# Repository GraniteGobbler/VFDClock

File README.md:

# VFDClock
A table clock with 7-segment VFD tubes running on an ESP32-S3 MCU.

## Showcase

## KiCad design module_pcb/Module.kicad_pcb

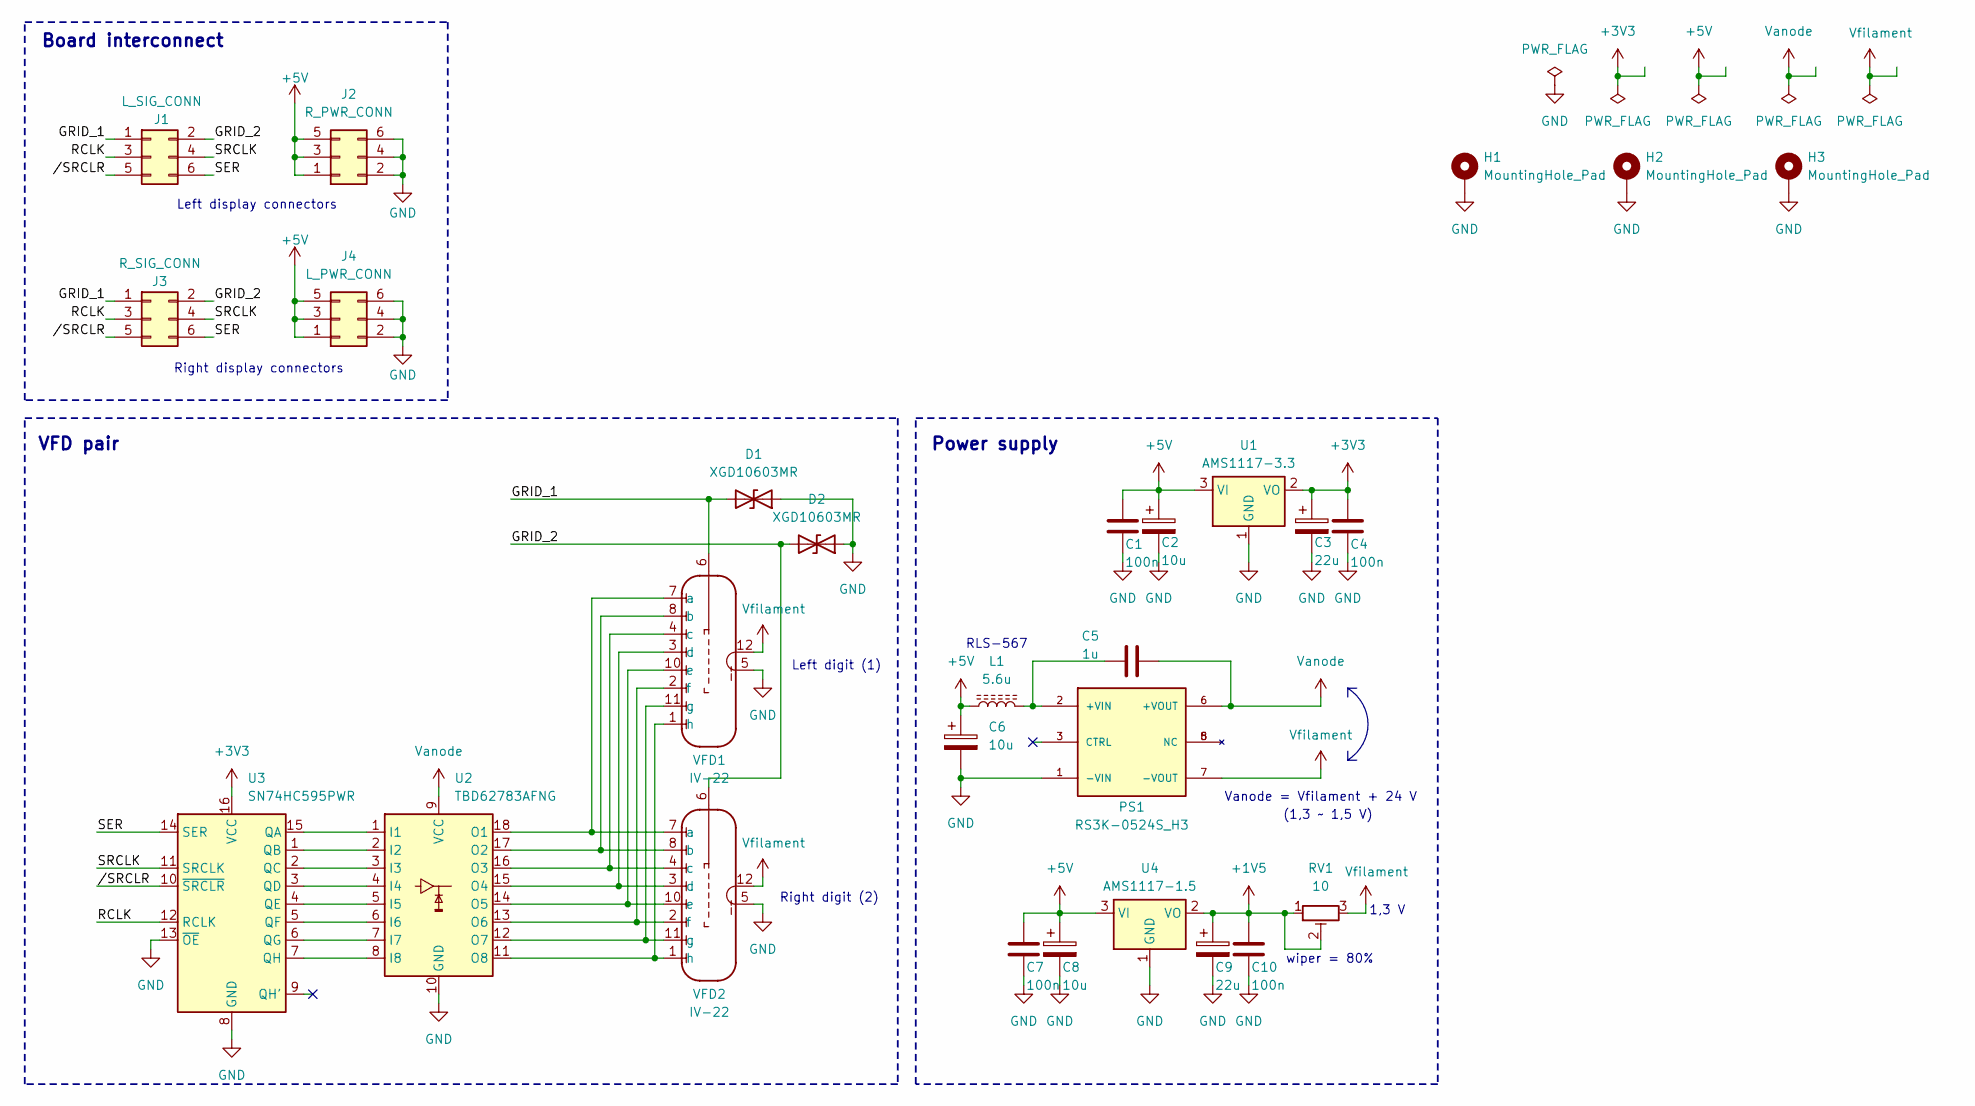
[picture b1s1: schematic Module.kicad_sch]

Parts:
C1, C4, C7, C10: 100n; C_0805_2012Metric
C2, C6, C8: 10u; CP_EIA-3216-18_Kemet-A
C3, C9: 22u; CP_EIA-3216-18_Kemet-A
C5: 1u; C_0805_2012Metric
D1, D2: XGD10603MR; D_0603_1608Metric
H1, H2, H3: MountingHole_Pad; MountingHole_3.2mm_M3_ISO14580_Pad_TopBottom
J1: L_SIG_CONN; PinSocket_2x03_P2.54mm_Horizontal
J2: R_PWR_CONN; PinSocket_2x03_P2.54mm_Horizontal
J3: R_SIG_CONN; PinSocket_2x03_P2.54mm_Horizontal
J4: L_PWR_CONN; PinSocket_2x03_P2.54mm_Horizontal
L1: 5.6u; L_1812_4532Metric
PS1: RS3K-0524S_H3; CONV_RS3K-0524S_H3; PARTREV 2-2024
RV1: 10; Potentiometer_Bourns_3339P_Vertical
U1: AMS1117-3.3; SOT-223-3_TabPin2
U2: TBD62783AFNG; SSOP-18_4.4x6.5mm_P0.65mm
U3: SN74HC595PWR; TSSOP-16_4.4x5mm_P0.65mm
U4: AMS1117-1.5; SOT-223-3_TabPin2
VFD1, VFD2: IV-22; PinSocket_1x12_P2.54mm_Vertical

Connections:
+1V5: C9.1, C10.1, RV1.1, RV1.2, U4.2 (VO)
+3V3: C3.1, C4.1, U1.2 (VO), U3.16 (VCC)
+5V: C1.1, C2.1, C6.1, C7.1, C8.1, J2.1, J2.3, J2.5, J4.1, J4.3, J4.5, L1.1, U1.3 (VI), U4.3 (VI)
/GRID_1: D1.2 (A2), J1.1, J3.1, VFD1.6
/GRID_2: D2.2 (A2), J1.2, J3.2, VFD2.6
/RCLK: J1.3, J3.3, U3.12 (RCLK)
/SER: J1.6, J3.6, U3.14 (SER)
/SRCLK: J1.4, J3.4, U3.11 (SRCLK)
//SRCLR: J1.5, J3.5, U3.10 (~SRCLR)
GND: C1.2, C2.2, C3.2, C4.2, C6.2, C7.2, C8.2, C9.2, C10.2, D1.1 (A1), D2.1 (A1), H1.1, H2.1, H3.1, J2.2, J2.4, J2.6, J4.2, J4.4, J4.6, PS1.1 (-VIN), U1.1 (GND), U2.10 (GND), U3.8 (GND), U3.13 (~OE), U4.1 (GND), VFD1.5, VFD2.5
unnamed: C5.1, L1.2, PS1.2 (+VIN)
unnamed: U2.1 (I1), U3.15 (QA)
unnamed: U2.2 (I2), U3.1 (QB)
unnamed: U2.3 (I3), U3.2 (QC)
unnamed: U2.4 (I4), U3.3 (QD)
unnamed: U2.5 (I5), U3.4 (QE)
unnamed: U2.6 (I6), U3.5 (QF)
unnamed: U2.7 (I7), U3.6 (QG)
unnamed: U2.8 (I8), U3.7 (QH)
unnamed: U2.18 (O1), VFD1.7 (a), VFD2.7 (a)
unnamed: U2.17 (O2), VFD1.8 (b), VFD2.8 (b)
unnamed: U2.16 (O3), VFD1.4 (c), VFD2.4 (c)
unnamed: U2.15 (O4), VFD1.3 (d), VFD2.3 (d)
unnamed: U2.14 (O5), VFD1.10 (e), VFD2.10 (e)
unnamed: U2.13 (O6), VFD1.2 (f), VFD2.2 (f)
unnamed: U2.12 (O7), VFD1.11 (g), VFD2.11 (g)
unnamed: U2.11 (O8), VFD1.1 (h), VFD2.1 (h)
Vanode: C5.2, PS1.6 (+VOUT), U2.9 (VCC)
Vfilament: PS1.7 (-VOUT), RV1.3, VFD1.12, VFD2.12

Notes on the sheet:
Right digit (2)
Left digit (1)
RLS-567
Power supply
Vanode = Vfilament + 24 V
1,3 V
VFD pair
Board interconnect
wiper = 80%
(1,3 ~ 1,5 V)
Left display connectors
Right display connectors

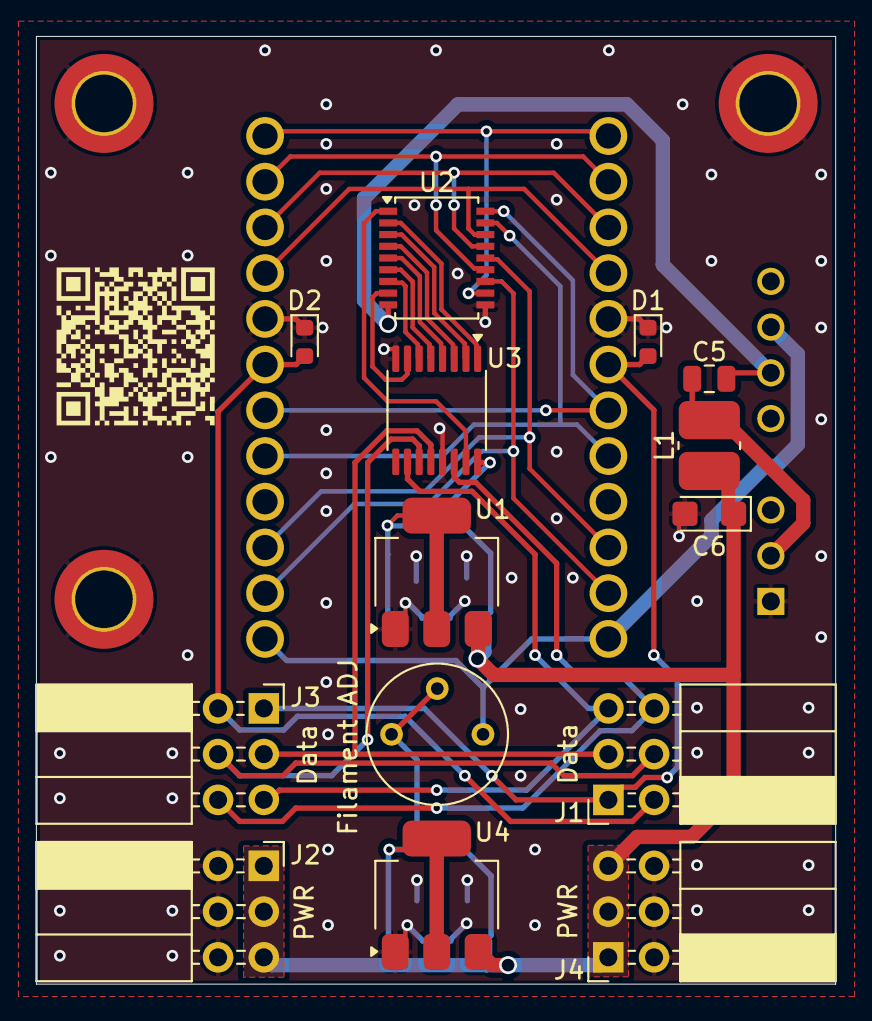
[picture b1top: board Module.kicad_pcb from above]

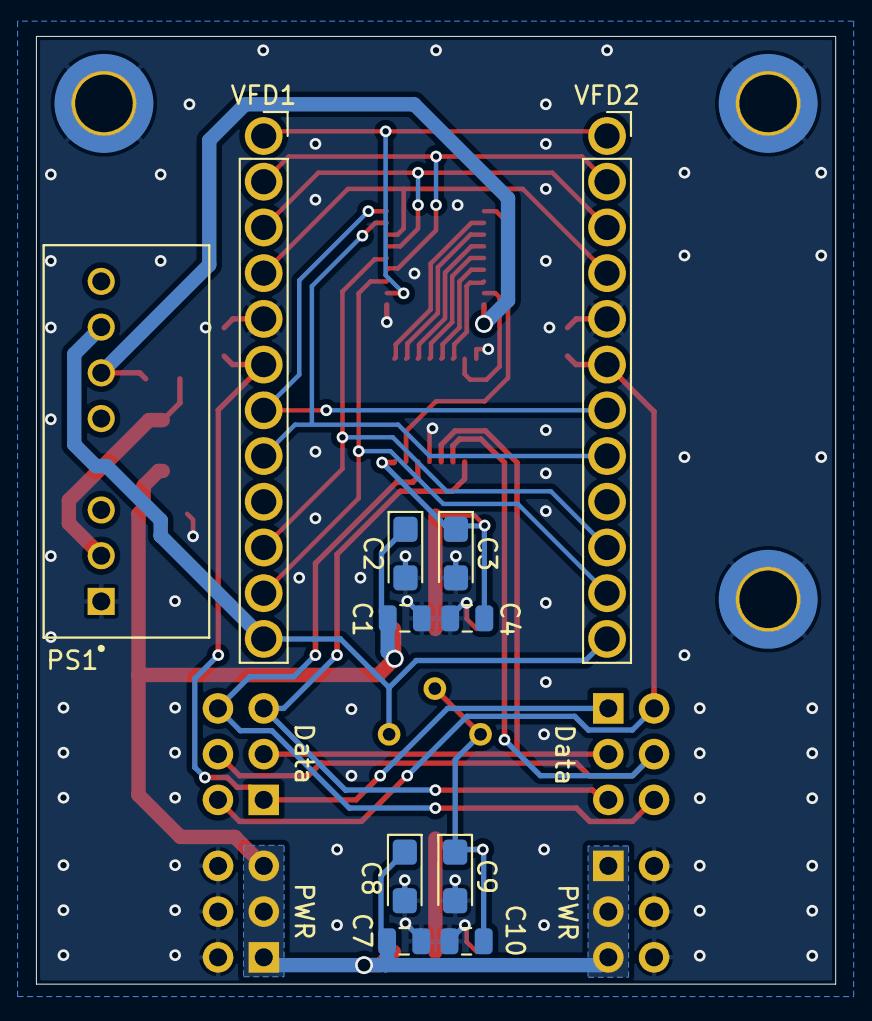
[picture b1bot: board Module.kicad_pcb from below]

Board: 2 copper layers, 44.4 x 52.7 mm, 28 parts (11 on the bottom side), 29 nets.

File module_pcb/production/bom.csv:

Designator,Footprint,Quantity,Value,LCSC Part #
"C1, C10, C4, C7",0805,4,100n,
"C2, C6, C8",CP_EIA-3216-18_Kemet-A,3,10u,
"C3, C9",CP_EIA-3216-18_Kemet-A,2,22u,
C5,0805,1,1u,
"D1, D2",0603,2,XGD10603MR,
J1,PinSocket_2x03_P2.54mm_Horizontal,1,L_SIG_CONN,
J2,PinSocket_2x03_P2.54mm_Horizontal,1,R_PWR_CONN,
J3,PinSocket_2x03_P2.54mm_Horizontal,1,R_SIG_CONN,
J4,PinSocket_2x03_P2.54mm_Horizontal,1,L_PWR_CONN,
L1,1812,1,5.6u,
PS1,CONV_RS3K-0524S_H3,1,RS3K-0524S_H3,
RV1,Potentiometer_Bourns_3339P_Vertical,1,10,
U1,SOT-223-3_TabPin2,1,AMS1117-3.3,
U2,SSOP-18_4.4x6.5mm_P0.65mm,1,TBD62783AFNG,
U3,TSSOP-16_4.4x5mm_P0.65mm,1,SN74HC595PWR,
U4,SOT-223-3_TabPin2,1,AMS1117-1.5,
"VFD1, VFD2",PinSocket_1x12_P2.54mm_Vertical,2,IV-22,

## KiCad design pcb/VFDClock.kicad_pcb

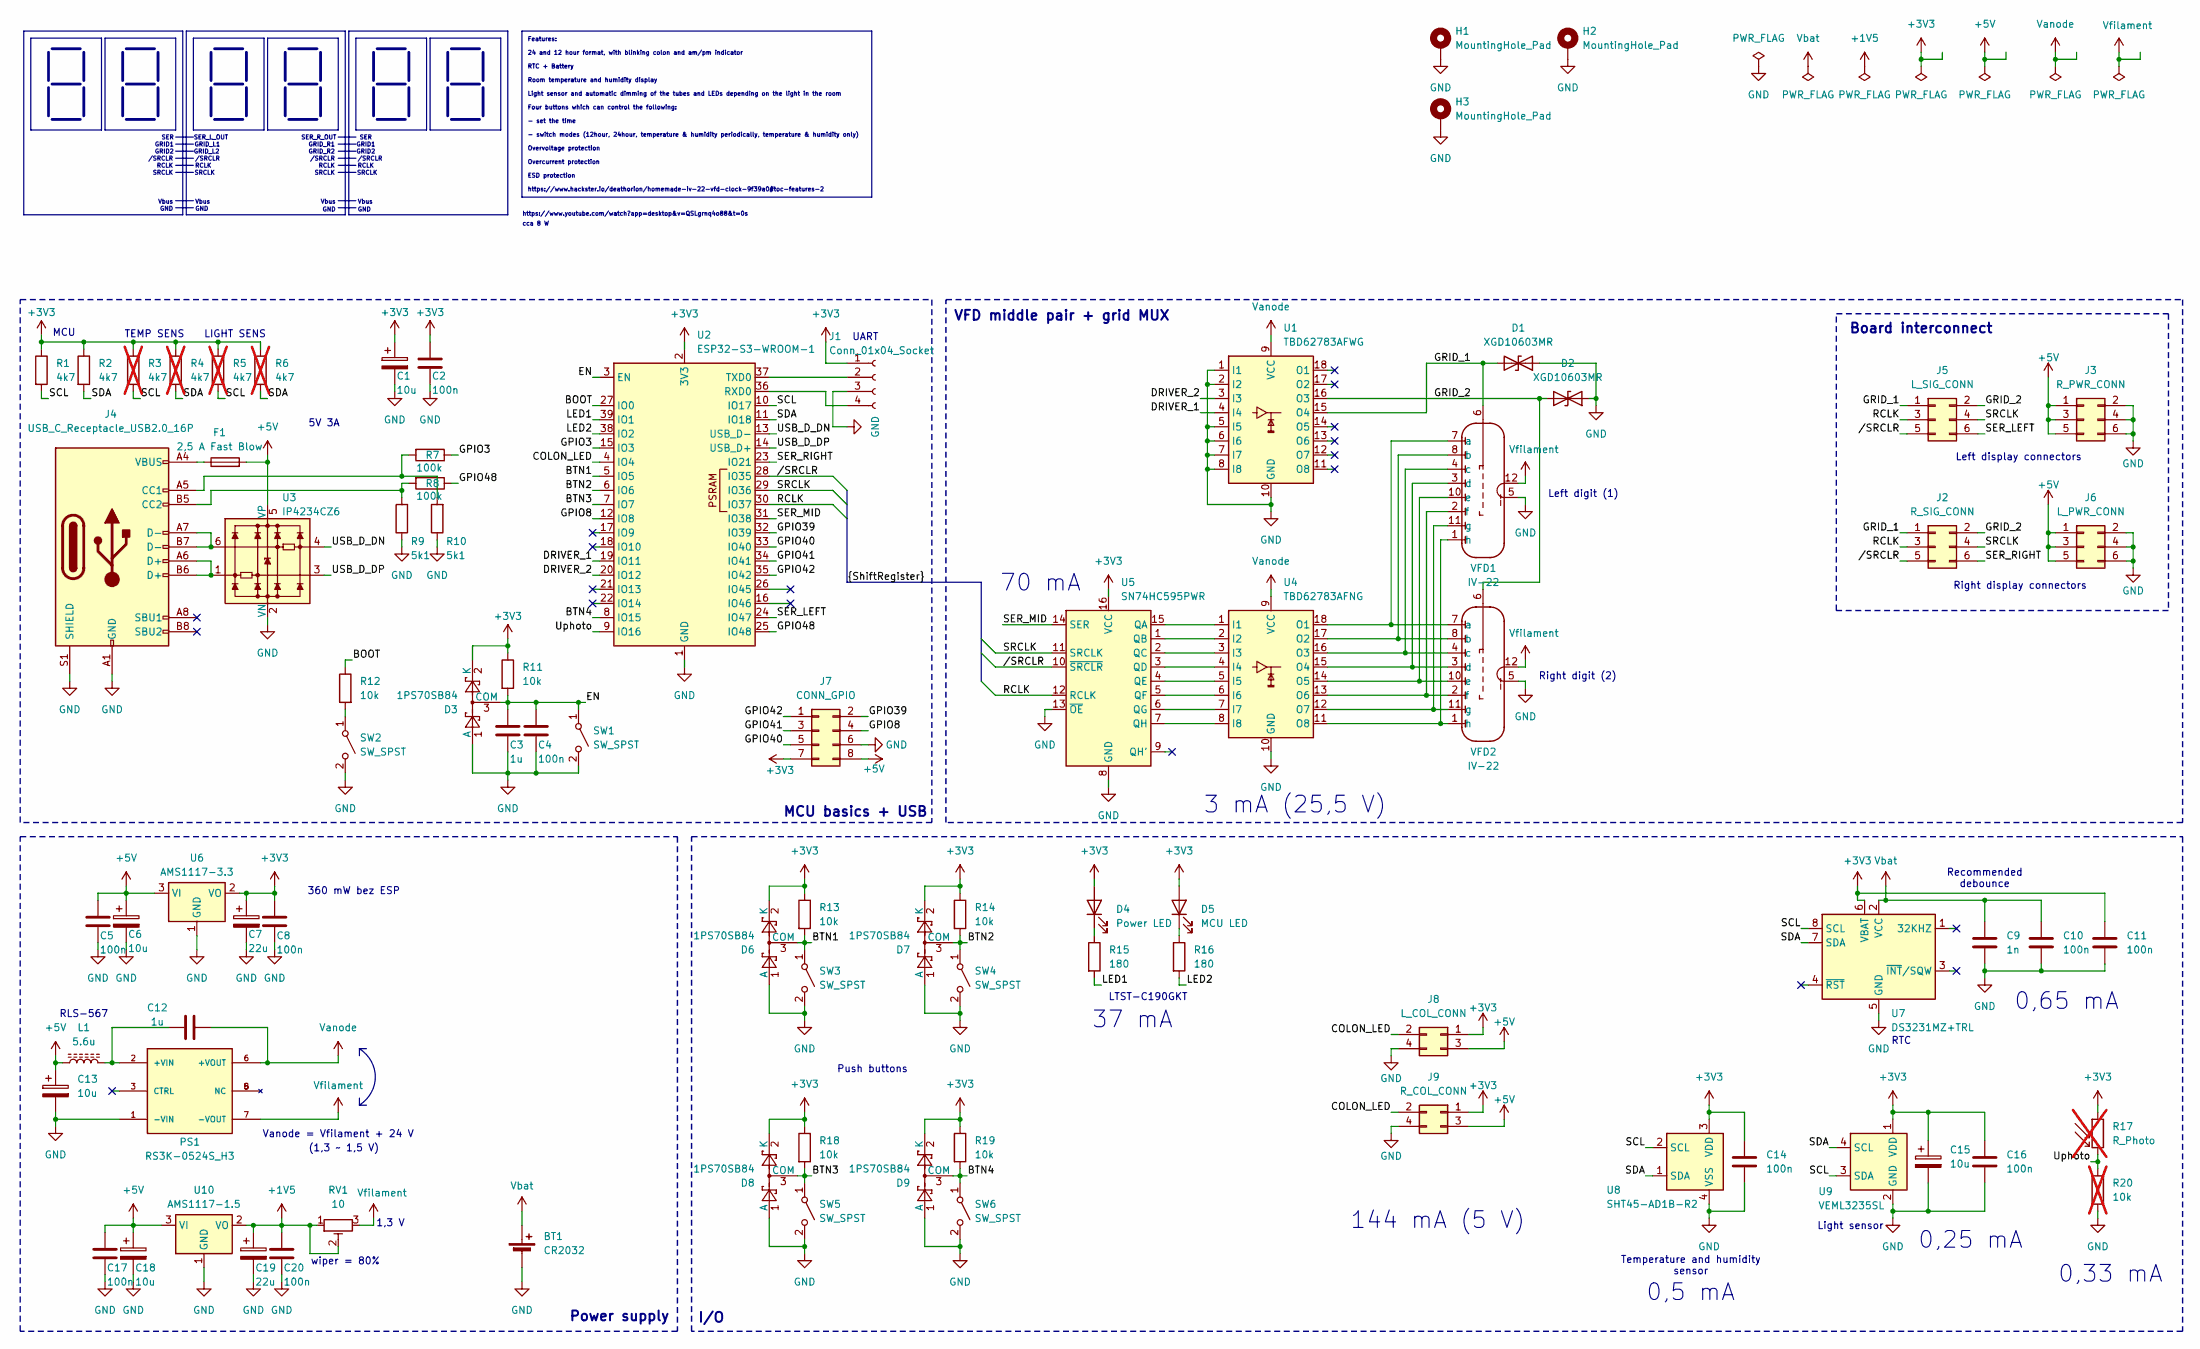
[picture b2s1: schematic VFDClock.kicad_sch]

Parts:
BT1: CR2032; BatteryHolder_Keystone_3034_1x20mm
C1, C6, C13, C15, C18: 10u; CP_EIA-3216-18_Kemet-A
C2, C4, C5, C8, C10, C11, C14, C16, C17, C20: 100n; C_0805_2012Metric
C3, C12: 1u; C_0805_2012Metric
C7, C19: 22u; CP_EIA-3216-18_Kemet-A
C9: 1n; C_0805_2012Metric
D1, D2: XGD10603MR; D_0603_1608Metric
D3, D6, D7, D8, D9: 1PS70SB84; SOT-323_SC-70
D4: Power LED; LED_0603_1608Metric
D5: MCU LED; LED_0603_1608Metric
F1: 2,5 A Fast Blow; Fuse_0603_1608Metric
H1, H2, H3: MountingHole_Pad; MountingHole_3.2mm_M3_ISO14580_Pad_TopBottom
J1: Conn_01x04_Socket; PinSocket_2x02_P2.54mm_Vertical_SMD
J2: R_SIG_CONN; PinHeader_2x03_P2.54mm_Horizontal
J3: R_PWR_CONN; PinHeader_2x03_P2.54mm_Horizontal
J4: USB_C_Receptacle_USB2.0_16P; CUI_UJ20-C-V-C-2-SMT-TR
J5: L_SIG_CONN; PinHeader_2x03_P2.54mm_Horizontal
J6: L_PWR_CONN; PinHeader_2x03_P2.54mm_Horizontal
J7: CONN_GPIO; PinSocket_2x04_P2.54mm_Vertical_SMD
J8: L_COL_CONN; JST_XH_B4B-XH-A_1x04_P2.50mm_Vertical
J9: R_COL_CONN; JST_XH_B4B-XH-A_1x04_P2.50mm_Vertical
L1: 5.6u; L_1812_4532Metric
PS1: RS3K-0524S_H3; CONV_RS3K-0524S_H3; PARTREV 2-2024
R1, R2: 4k7; R_0805_2012Metric
R3, R4, R5, R6: 4k7; R_0805_2012Metric; not fitted
R7, R8: 100k; R_0805_2012Metric
R9, R10: 5k1; R_0805_2012Metric
R11, R12, R13, R14, R18, R19: 10k; R_0805_2012Metric
R15, R16: 180; R_0805_2012Metric
R17: R_Photo; R_LDR_5.1x4.3mm_P3.4mm_Vertical; not fitted
R20: 10k; R_0805_2012Metric; not fitted
RV1: 10; Potentiometer_Bourns_3339P_Vertical
SW1, SW2: SW_SPST; SW_SPST_PTS810
SW3, SW4, SW5, SW6: SW_SPST; SW_Tactile_SPST_Angled_PTS645Vx83-2LFS
U1: TBD62783AFWG; SSOP-18_4.4x6.5mm_P0.65mm
U2: ESP32-S3-WROOM-1
U3: IP4234CZ6; SC-74-6_1.55x2.9mm_P0.95mm
U4: TBD62783AFNG; SSOP-18_4.4x6.5mm_P0.65mm
U5: SN74HC595PWR; TSSOP-16_4.4x5mm_P0.65mm
U6: AMS1117-3.3; SOT-223-3_TabPin2
U7: DS3231MZ+TRL; SOIC-8_3.9x4.9mm_P1.27mm
U8: SHT45-AD1B-R2; Sensirion_DFN-4_1.5x1.5mm_P0.8mm_SHT4x_NoCentralPad
U9: VEML3235SL; VEML3235SL_Horizontal
U10: AMS1117-1.5; SOT-223-3_TabPin2
VFD1, VFD2: IV-22; PinSocket_1x12_P2.54mm_Vertical

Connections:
+1V5: C19.1, C20.1, RV1.1, RV1.2, U10.2 (VO)
+3V3: C1.1, C2.1, C7.1, C8.1, C11.1, C14.1, C15.1, C16.1, D3.2 (K), D4.2 (A), D5.2 (A), D6.2 (K), D7.2 (K), D8.2 (K), D9.2 (K), J1.1, J7.7, J8.1, J9.1, R1.1, R2.1, R3.1, R4.1, R5.1, R6.1, R11.1, R13.1, R14.1, R17.1, R18.1, R19.1, U2.2 (3V3), U5.16 (VCC), U6.2 (VO), U7.6 (VBAT), U8.3 (VDD), U9.1 (VDD)
+5V: C5.1, C6.1, C13.1, C17.1, C18.1, F1.2, J3.1, J3.3, J3.5, J6.1, J6.3, J6.5, J7.8, J8.3, J9.3, L1.1, U3.5 (VP), U6.3 (VI), U10.3 (VI)
/BOOT: R12.1, U2.27 (IO0)
/BTN1: D6.3 (COM), R13.2, SW3.1 (A), U2.5 (IO5)
/BTN2: D7.3 (COM), R14.2, SW4.1 (A), U2.6 (IO6)
/BTN3: D8.3 (COM), R18.2, SW5.1 (A), U2.7 (IO7)
/BTN4: D9.3 (COM), R19.2, SW6.1 (A), U2.8 (IO15)
/COLON_LED: J8.2, J9.2, U2.4 (IO4)
/DRIVER_1: U1.4 (I4), U2.19 (IO11)
/DRIVER_2: U1.3 (I3), U2.20 (IO12)
/EN: C3.1, C4.1, D3.3 (COM), R11.2, SW1.1 (A), U2.3 (EN)
/GPIO3: R7.1, U2.15 (IO3)
/GPIO8: J7.4, U2.12 (IO8)
/GPIO39: J7.2, U2.32 (IO39)
/GPIO40: J7.5, U2.33 (IO40)
/GPIO41: J7.3, U2.34 (IO41)
/GPIO42: J7.1, U2.35 (IO42)
/GPIO48: R8.1, U2.25 (IO48)
/GRID_1: D1.2 (A2), J2.1, J5.1, U1.15 (O4), VFD1.6
/GRID_2: D2.2 (A2), J2.2, J5.2, U1.16 (O3), VFD2.6
/LED1: R15.2, U2.39 (IO1)
/LED2: R16.2, U2.38 (IO2)
/RCLK: J2.3, J5.3, U2.30 (IO37), U5.12 (RCLK)
/SCL: R1.2, R3.2, R5.2, U2.10 (IO17), U7.8 (SCL), U8.2 (SCL), U9.3 (SDA)
/SDA: R2.2, R4.2, R6.2, U2.11 (IO18), U7.7 (SDA), U8.1 (SDA), U9.4 (SCL)
/SER_LEFT: J5.6, U2.24 (IO47)
/SER_MID: U2.31 (IO38), U5.14 (SER)
/SER_RIGHT: J2.6, U2.23 (IO21)
/SRCLK: J2.4, J5.4, U2.29 (IO36), U5.11 (SRCLK)
/USB_D_DN: U2.13 (USB_D-), U3.4
/USB_D_DP: U2.14 (USB_D+), U3.3
/Uphoto: R17.2, R20.1, U2.9 (IO16)
//SRCLR: J2.5, J5.5, U2.28 (IO35), U5.10 (~SRCLR)
GND: BT1.2 (-), C1.2, C2.2, C3.2, C4.2, C5.2, C6.2, C7.2, C8.2, C9.2, C10.2, C11.2, C13.2, C14.2, C15.2, C16.2, C17.2, C18.2, C19.2, C20.2, D1.1 (A1), D2.1 (A1), D3.1 (A), D6.1 (A), D7.1 (A), D8.1 (A), D9.1 (A), H1.1, H2.1, H3.1, J1.3, J3.2, J3.4, J3.6, J4.A1 (GND), J4.A12 (GND), J4.B1 (GND), J4.B12 (GND), J4.S1 (SHIELD), J6.2, J6.4, J6.6, J7.6, J8.4, J9.4, PS1.1 (-VIN), R9.1, R10.1, R20.2, SW1.2 (B), SW2.2 (B), SW3.2 (B), SW4.2 (B), SW5.2 (B), SW6.2 (B), U1.1 (I1), U1.2 (I2), U1.5 (I5), U1.6 (I6), U1.7 (I7), U1.8 (I8), U1.10 (GND), U2.1 (GND), U2.40 (GND), U2.41 (GND), U3.2 (VN), U4.10 (GND), U5.8 (GND), U5.13 (~OE), U6.1 (GND), U7.5 (GND), U8.4 (VSS), U9.2 (GND), U10.1 (GND), VFD1.5, VFD2.5
unnamed: D4.1 (K), R15.1
unnamed: D5.1 (K), R16.1
unnamed: F1.1, J4.A4 (VBUS), J4.A9 (VBUS), J4.B4 (VBUS), J4.B9 (VBUS)
unnamed: J1.2, U2.37 (TXD0)
unnamed: J1.4, U2.36 (RXD0)
unnamed: J4.A5 (CC1), R7.2, R10.2
unnamed: J4.B5 (CC2), R8.2, R9.2
unnamed: J4.A6 (D+), J4.B6 (D+), U3.1
unnamed: J4.A7 (D-), J4.B7 (D-), U3.6
unnamed: C12.1, L1.2, PS1.2 (+VIN)
unnamed: R12.2, SW2.1 (A)
unnamed: U4.1 (I1), U5.15 (QA)
unnamed: U4.2 (I2), U5.1 (QB)
unnamed: U4.3 (I3), U5.2 (QC)
unnamed: U4.4 (I4), U5.3 (QD)
unnamed: U4.5 (I5), U5.4 (QE)
unnamed: U4.6 (I6), U5.5 (QF)
unnamed: U4.7 (I7), U5.6 (QG)
unnamed: U4.8 (I8), U5.7 (QH)
unnamed: U4.18 (O1), VFD1.7 (a), VFD2.7 (a)
unnamed: U4.17 (O2), VFD1.8 (b), VFD2.8 (b)
unnamed: U4.16 (O3), VFD1.4 (c), VFD2.4 (c)
unnamed: U4.15 (O4), VFD1.3 (d), VFD2.3 (d)
unnamed: U4.14 (O5), VFD1.10 (e), VFD2.10 (e)
unnamed: U4.13 (O6), VFD1.2 (f), VFD2.2 (f)
unnamed: U4.12 (O7), VFD1.11 (g), VFD2.11 (g)
unnamed: U4.11 (O8), VFD1.1 (h), VFD2.1 (h)
Vanode: C12.2, PS1.6 (+VOUT), U1.9 (VCC), U4.9 (VCC)
Vbat: BT1.1 (+), C9.1, C10.1, U7.2 (VCC)
Vfilament: PS1.7 (-VOUT), RV1.3, VFD1.12, VFD2.12

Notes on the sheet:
TEMP SENS
0,5 mA
Right digit (2)
GRID_R2
3 mA (25,5 V)
0,65 mA
Left digit (1)
Vbus
Push buttons
SRCLK
RTC
Temperature and humidity sensor
RLS-567
MCU
Power supply
UART
GND
0,25 mA
37 mA
GRID2
Vanode = Vfilament + 24 V
RCLK
1,3 V
VFD middle pair + grid MUX
MCU basics + USB
SER_R_OUT
Board interconnect
GRID_R1
SER_L_OUT
wiper = 80%
(1,3 ~ 1,5 V)
144 mA (5 V)
/SRCLR
GRID1
https://www.youtube.com/watch?app=desktop&v=QSLgrnq4o88&t=0s
I/O
LIGHT SENS
GRID_L1
SER
GRID_L2

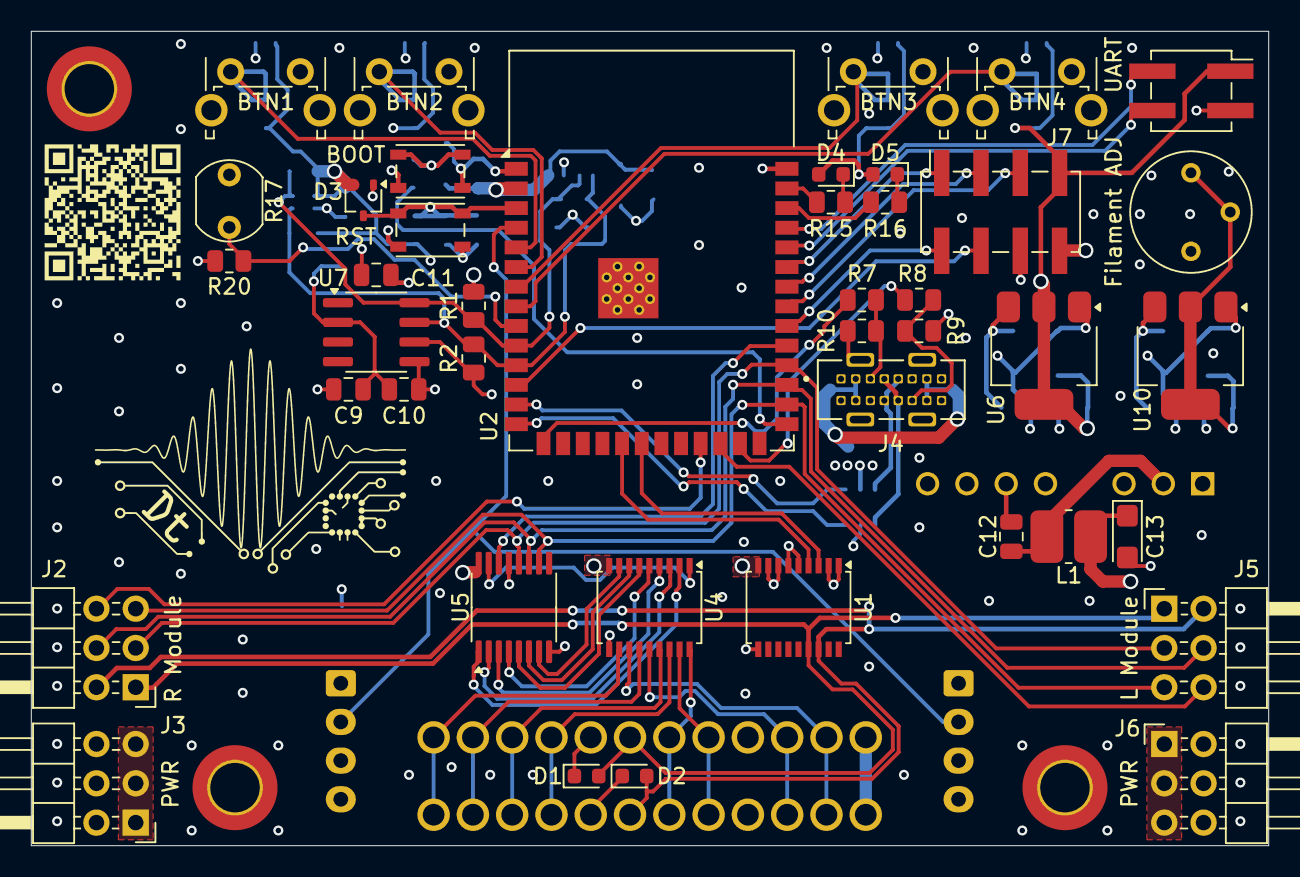
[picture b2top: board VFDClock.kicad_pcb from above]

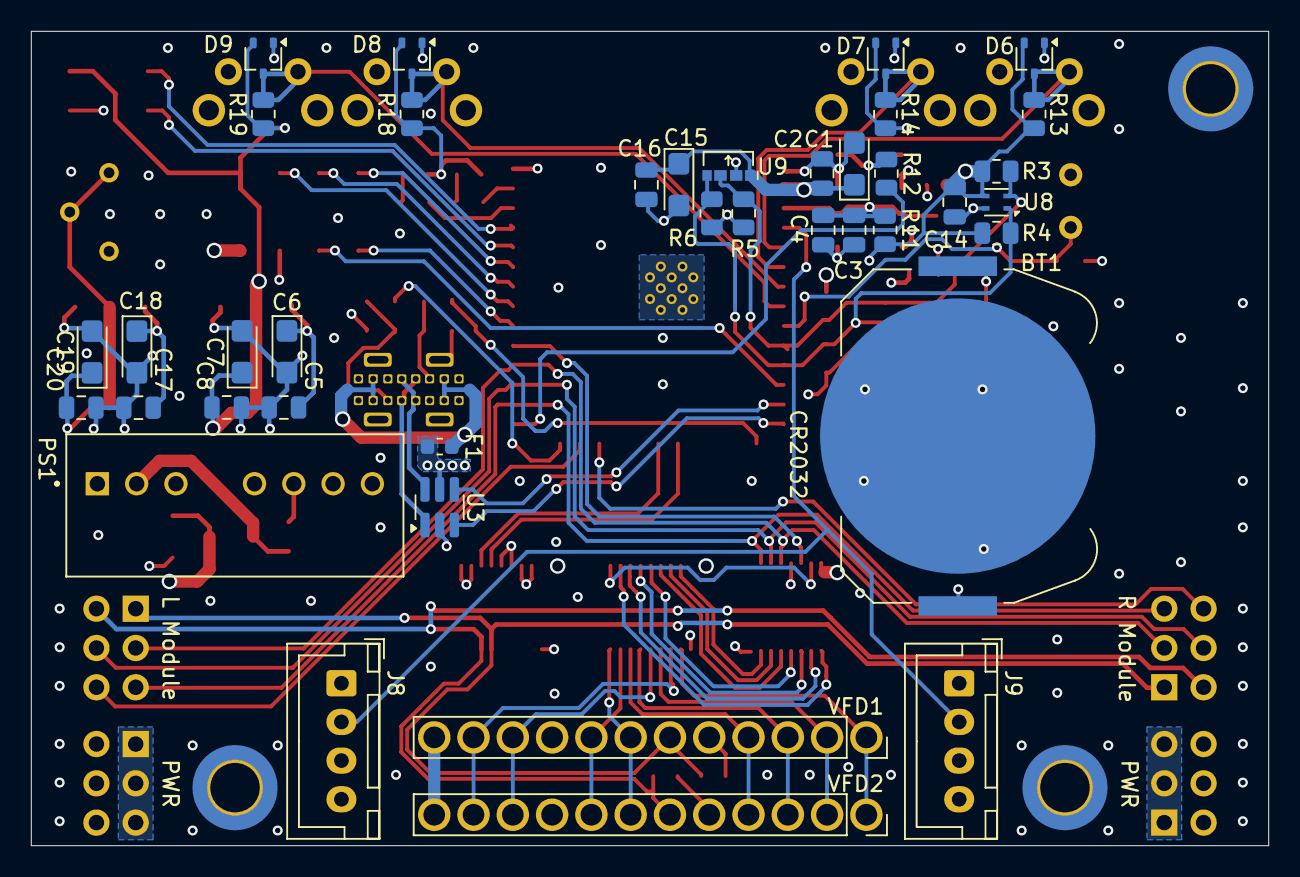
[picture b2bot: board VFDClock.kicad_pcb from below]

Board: 4 copper layers, 80.0 x 52.7 mm, 84 parts (39 on the bottom side), 65 nets.

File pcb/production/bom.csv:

Designator,Footprint,Quantity,Value,LCSC Part #
BT1,BatteryHolder_Keystone_3034_1x20mm,1,CR2032,
"C1, C13, C15, C18, C6",CP_EIA-3216-18_Kemet-A,5,10u,
"C10, C11, C14, C16, C17, C2, C20, C4, C5, C8",0805,10,100n,
"C12, C3",0805,2,1u,
"C19, C7",CP_EIA-3216-18_Kemet-A,2,22u,
C9,0805,1,1n,
"D1, D2",0603,2,XGD10603MR,
"D3, D6, D7, D8, D9",SOT-323_SC-70,5,1PS70SB84,
D4,0603,1,Power LED,
D5,0603,1,MCU LED,
F1,0603,1,"2,5 A Fast Blow",
J1,PinSocket_2x02_P2.54mm_Vertical_SMD,1,Conn_01x04_Socket,
J2,PinHeader_2x03_P2.54mm_Horizontal,1,R_SIG_CONN,
J3,PinHeader_2x03_P2.54mm_Horizontal,1,R_PWR_CONN,
J4,CUI_UJ20-C-V-C-2-SMT-TR,1,USB_C_Receptacle_USB2.0_16P,
J5,PinHeader_2x03_P2.54mm_Horizontal,1,L_SIG_CONN,
J6,PinHeader_2x03_P2.54mm_Horizontal,1,L_PWR_CONN,
J7,PinSocket_2x04_P2.54mm_Vertical_SMD,1,CONN_GPIO,
J8,JST_XH_B4B-XH-A_1x04_P2.50mm_Vertical,1,L_COL_CONN,
J9,JST_XH_B4B-XH-A_1x04_P2.50mm_Vertical,1,R_COL_CONN,
L1,1812,1,5.6u,
PS1,CONV_RS3K-0524S_H3,1,RS3K-0524S_H3,
"R1, R2, R3, R4, R5, R6",0805,6,4k7,
"R10, R9",0805,2,5k1,
"R11, R12, R13, R14, R18, R19, R20",0805,7,10k,
"R15, R16",0805,2,180,
R17,R_LDR_5.1x4.3mm_P3.4mm_Vertical,1,R_Photo,
"R7, R8",0805,2,100k,
RV1,Potentiometer_Bourns_3339P_Vertical,1,10,
"SW1, SW2",SW_SPST_PTS810,2,SW_SPST,
"SW3, SW4, SW5, SW6",SW_Tactile_SPST_Angled_PTS645Vx83-2LFS,4,SW_SPST,
U1,SSOP-18_4.4x6.5mm_P0.65mm,1,TBD62783AFWG,
U10,SOT-223-3_TabPin2,1,AMS1117-1.5,
U2,ESP32-S3-WROOM-1,1,ESP32-S3-WROOM-1,
U3,SC-74-6_1.55x2.9mm_P0.95mm,1,IP4234CZ6,
U4,SSOP-18_4.4x6.5mm_P0.65mm,1,TBD62783AFNG,
U5,TSSOP-16_4.4x5mm_P0.65mm,1,SN74HC595PWR,
U6,SOT-223-3_TabPin2,1,AMS1117-3.3,
U7,SOIC-8_3.9x4.9mm_P1.27mm,1,DS3231MZ+TRL,
U8,Sensirion_DFN-4_1.5x1.5mm_P0.8mm_SHT4x_NoCentralPad,1,SHT45-AD1B-R2,
U9,VEML3235SL_Horizontal,1,VEML3235SL,
"VFD1, VFD2",PinSocket_1x12_P2.54mm_Vertical,2,IV-22,

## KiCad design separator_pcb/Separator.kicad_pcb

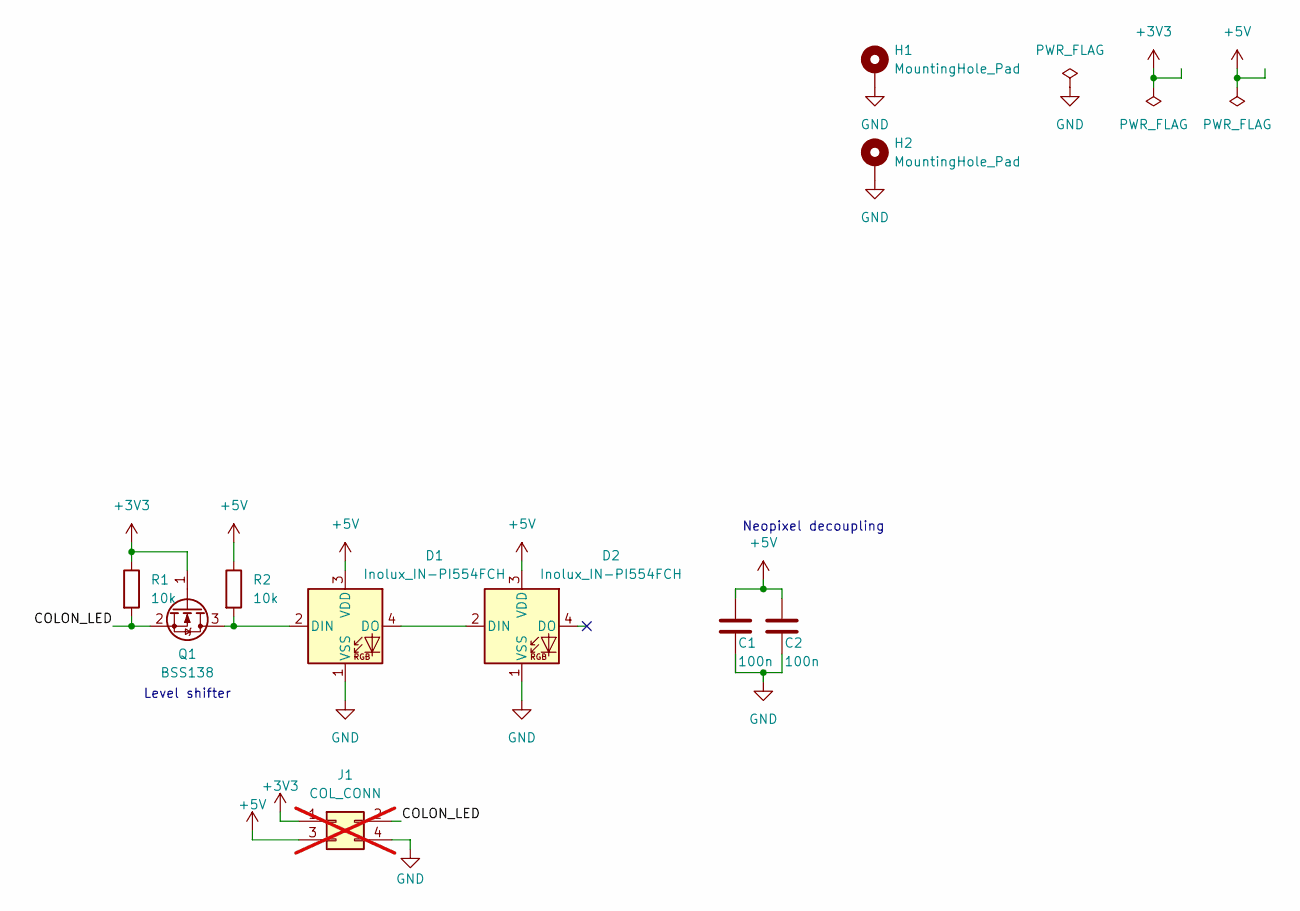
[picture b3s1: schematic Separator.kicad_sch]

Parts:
C1, C2: 100n; C_0805_2012Metric
D1, D2: Inolux_IN-PI554FCH; LED_Inolux_IN-PI554FCH_PLCC4_5.0x5.0mm_P3.2mm
H1, H2: MountingHole_Pad; MountingHole_3.2mm_M3_ISO14580_Pad_TopBottom
J1: COL_CONN; PinHeader_2x02_P2.00mm_Vertical; not fitted
Q1: BSS138; SOT-23
R1, R2: 10k; R_0805_2012Metric

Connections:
+3V3: J1.1, Q1.1 (G), R1.1
+5V: C1.1, C2.1, D1.3 (VDD), D2.3 (VDD), J1.3, R2.1
/COLON_LED: J1.2, Q1.2 (S), R1.2
GND: C1.2, C2.2, D1.1 (VSS), D2.1 (VSS), H1.1, H2.1, J1.4
unnamed: D1.2 (DIN), Q1.3 (D), R2.2
unnamed: D1.4 (DO), D2.2 (DIN)

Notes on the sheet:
Neopixel decoupling
Level shifter

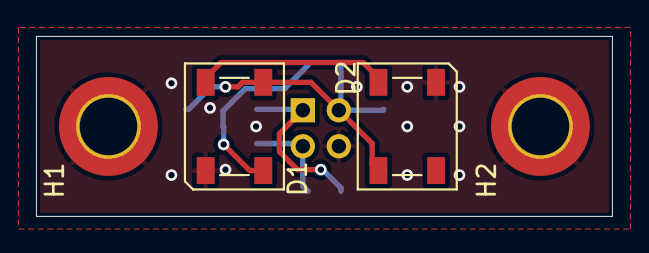
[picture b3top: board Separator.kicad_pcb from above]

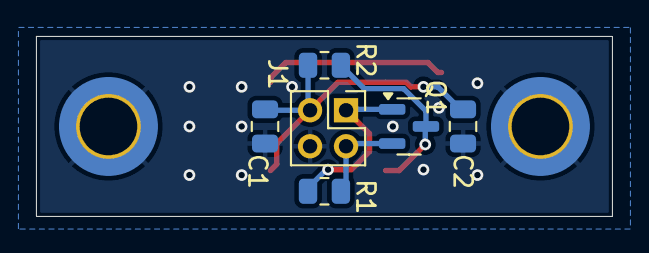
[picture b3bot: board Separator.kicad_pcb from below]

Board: 2 copper layers, 32.0 x 10.0 mm, 10 parts (6 on the bottom side), 6 nets.

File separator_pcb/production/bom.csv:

Designator,Footprint,Quantity,Value,LCSC Part #
"C1, C2",0805,2,100n,
"D1, D2",LED_Inolux_IN-PI554FCH_PLCC4_5.0x5.0mm_P3.2mm,2,Inolux_IN-PI554FCH,
J1,PinHeader_2x02_P2.00mm_Vertical,1,COL_CONN,
Q1,SOT-23,1,BSS138,
"R1, R2",0805,2,10k,

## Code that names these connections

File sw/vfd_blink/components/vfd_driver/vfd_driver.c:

/*     
    This is a driver for IV-22 VFD tubes, based on the SN74HC595 8-bit shift register.
    

    ---------------------   --------------------- 
    |                   |   |                   |
    |   |-----a-----|   |   |   |-----a-----|   |
    |   |           |   |   |   |           |   |
    |   b           c   |   |   b           c   |
    |   |           |   |   |   |           |   |
    |   |-----d-----|   |   |   |-----d-----|   |
    |   |           |   |   |   |           |   |
    |   e           f   |   |   e           f   |
    |   |           |   |   |   |           |   |
    |   |-----g-----|   |   |   |-----g-----|   |
    |                 h |   |                 h |
    |                   |   |                   |
    ---------------------   ---------------------

*/

#include "vfd_driver.h"

void vfd_info(void)
{
    ESP_LOGI("vfd_info", "IV-22 tube driver based on the SN74HC595 8-bit Shift Register");
}

void vfd_clear(void){
    gpio_set_level(SRCLR, 0); // Clear the shift register once
    gpio_set_level(SRCLR, 1);
}

void vfd_init(void){
    // GPIO config
    gpio_config_t GPIO_CONF_VFD;
    // Bit mask
    GPIO_CONF_VFD.pin_bit_mask = (1ULL << SER_LEFT) | (1ULL << SER_MID) | (1ULL << SER_RIGHT) |
                                 (1ULL << SRCLR) | (1ULL << SRCLK) | (1ULL << RCLK) |
                                 (1ULL << DRIVER1) | (1ULL << DRIVER2);
    // Pin mode
    GPIO_CONF_VFD.mode = GPIO_MODE_OUTPUT;
    // No pull-up/pull-down resistors.
    GPIO_CONF_VFD.pull_up_en = GPIO_PULLUP_DISABLE;
    GPIO_CONF_VFD.pull_down_en = GPIO_PULLDOWN_DISABLE;
    // No interrupt enabled.
    GPIO_CONF_VFD.intr_type = GPIO_INTR_DISABLE;
    // Configure the GPIO with the settings.
    gpio_config(&GPIO_CONF_VFD);

    vfd_info();
    vfd_clear();

    gpio_set_level(RCLK, 0);

}



void vfd_update(uint8_t value){

    for(uint8_t i = 0; i < sizeof(value) * 8; i++){

        gpio_set_level(SER_MID, value & 1); // Write LSB of value to SER

		value >>= 1;

		gpio_set_level(SRCLK, 1); // Tick the shift register storage
		gpio_set_level(SRCLK, 0);
    }

    gpio_set_level(RCLK, 1); // Send SR storage to output
	gpio_set_level(RCLK, 0);
}



void vfd_value(uint8_t value, bool digit_select){
    
    // Digit mux - DRIVER1 = tens, DRIVER2 = ones
    if(digit_select == 0){
        gpio_set_level(DRIVER1, 0);
        gpio_set_level(DRIVER2, 1);

        vfd_update(number_map[value % 10]); // Extract ones
    }
    else{
        gpio_set_level(DRIVER1, 1);
        gpio_set_level(DRIVER2, 0);

        vfd_update(number_map[value / 10]); // Extract tens
    }
    
}


void vfd_update_str(uint32_t value_buf){

    for(uint8_t i = 0; i < (sizeof(uint8_t) * 8); i++){
        
        gpio_set_level(SER_LEFT, value_buf & 1); // Write LSB of value to SER        
        gpio_set_level(SER_MID, value_buf & (1 << 8));
        gpio_set_level(SER_RIGHT, value_buf & (1 << 16));

        value_buf >>= 1;

        gpio_set_level(SRCLK, 1); // Tick the shift register storage
		gpio_set_level(SRCLK, 0);
    }

    gpio_set_level(RCLK, 1); // Send SR storage to output
	gpio_set_level(RCLK, 0);
}



void vfd_value_str(const char *input_str, bool position){
    
    uint32_t value_buf = 0; // Buffer variable for outputting triplets at once

    for(uint8_t i = 0; i < 3; i++){
        char character = input_str[2*i + position];
        
        if (character >= '0' && character <= '9'){
            // vfd_update_str(number_map[character - '0'], i);
            value_buf |= number_map[character - '0'] << (8*i);    // Shift 8*i times depending on if the character is 1st, 2nd or 3rd
        }
        else if (character >= 'a' && character <= 'z'){
            // vfd_update_str(character_map[character - 'a'], i);
            value_buf |= character_map[character - 'a'] << (8*i);
        }
        else if (character >= 'A' && character <= 'Z'){
            // vfd_update_str(character_map[character - 'A'], i);
            value_buf |= character_map[character - 'A'] << (8*i);
        }

        // Digit mux - DRIVER1 = tens, DRIVER2 = ones
        if(position == 0){  // 0 = left position, 1 = right position
            gpio_set_level(DRIVER1, 1);
            gpio_set_level(DRIVER2, 0);
        }
        else{
            gpio_set_level(DRIVER1, 0);
            gpio_set_level(DRIVER2, 1);
        }
    }  

    vfd_update_str(value_buf);
}

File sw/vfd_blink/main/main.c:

/* Includes */
#include <stdio.h>
#include <math.h>
#include <inttypes.h>
#include "esp_log.h"
#include "sdkconfig.h"
#include "freertos/FreeRTOS.h"
#include "freertos/task.h"
#include "esp_flash.h"
#include "esp_log.h"
#include "driver/gpio.h"
#include "esp_timer.h"

#include "vfd_driver.h"

/* Defines */
#define LED_Power   GPIO_NUM_1 // LED D4
#define LED_MCU     GPIO_NUM_2 // LED D5
#define BTN1        GPIO_NUM_5 // Rightmost button
#define BTN2        GPIO_NUM_6
#define BTN3        GPIO_NUM_7
#define BTN4        GPIO_NUM_15 // Leftmost button
#define VFD_REFRESH_PERIOD  10000 // 8333*2 = 16666 us = 60 fps

static const char* TAG = "VFDClock";
bool mux_select = 0;
uint8_t vfd_display_number = 0;
char vfd_display_string[] = "abcdef";   // Variable containing a string that is to be displayed


// Handles
TaskHandle_t ledBlinkTaskHandle = NULL;
TaskHandle_t CounterTaskHandle = NULL;


// Functions
/* LED Config */
void GPIOConfig(void){
    /*  GPIO Config */
    gpio_config_t GPIO_CONF_LED = 
    {
    .pin_bit_mask = (1ULL << LED_Power) | (1ULL << LED_MCU),    // Bit mask
    .mode = GPIO_MODE_OUTPUT,   // Pin mode
    .pull_up_en = GPIO_PULLUP_DISABLE,  // No pull-up/pull-down resistors.
    .pull_down_en = GPIO_PULLDOWN_DISABLE,
    .intr_type = GPIO_INTR_DISABLE, // No interrupt enabled.
    };

    gpio_config_t GPIO_CONF_BUTTONS = 
    {
    .pin_bit_mask = (1ULL << BTN1) | (1ULL << BTN2) | 
                    (1ULL << BTN3) | (1ULL << BTN4), // Bit mask
    .mode = GPIO_MODE_INPUT,   // Pin mode
    .pull_up_en = GPIO_PULLUP_DISABLE,  // No pull-up/pull-down resistors.
    .pull_down_en = GPIO_PULLDOWN_DISABLE,
    .intr_type = GPIO_INTR_DISABLE, // No interrupt enabled.
    };

    // Configure the GPIO with the settings.
    gpio_config(&GPIO_CONF_LED);
    gpio_config(&GPIO_CONF_BUTTONS);


}

/* Timer callbacks */
void mux_callback(void *param){

    // vfd_value(vfd_display_number, mux_select);
    vfd_value_str(vfd_display_string, mux_select);
    mux_select = !mux_select;
}




/* LED Blink Task*/
void ledBlinkTask(void *pvParameters){
    // Turn Power LED on when "power is present"
    gpio_set_level(LED_Power, 0); 

    ESP_LOGW("ledBlinkTask", "CORE ID: %d", xPortGetCoreID());

    while(1){
            // Toggle MCU LED (D5)
            gpio_set_level(LED_MCU, 0);
            // ESP_LOGI("ledBlinkTask", "MCU LED on");
            vTaskDelay(1000 / portTICK_PERIOD_MS);

            gpio_set_level(LED_MCU, 1);
            // ESP_LOGI("ledBlinkTask", "MCU LED off");
            vTaskDelay(1000 / portTICK_PERIOD_MS);
        }
}

/*Counter Task*/
void CounterTask(void *pvParameters){
    // uint8_t cnt = 0;
    char firstChar;
    while (1){

        if(gpio_get_level(BTN4) != 1){

            for(uint8_t j = 0; j < 12; j++){ // Repeat 6 times

                firstChar = vfd_display_string[0]; // First character of the string

                for (uint8_t i = 1; i < 7; i++){
                    vfd_display_string[i - 1] = vfd_display_string[i];
                }
                vfd_display_string[5] = firstChar;

                vTaskDelay(pdMS_TO_TICKS(400));
            }
        }
        // sprintf(vfd_display_string, "klmnop");
        
        // vfd_display_number = (cnt++) % 100;

        vTaskDelay(pdMS_TO_TICKS(100));
    }
}

void app_main(void){
    ESP_LOGW(TAG, "==== START ===");

    /* Timer config */
    const esp_timer_create_args_t mux_timer_args =
    {
        .callback = &mux_callback,
        .name = "Mux Timer Interrupt"
    };

    esp_timer_handle_t mux_timer_handle;
    esp_timer_create(&mux_timer_args, &mux_timer_handle);
    esp_timer_start_periodic(mux_timer_handle, VFD_REFRESH_PERIOD); // 8 ms period
    


    /* Init */
    GPIOConfig();
    vfd_init();

    
    /*  FreeRTOS tasks  */
    xTaskCreate(
        ledBlinkTask,        // Task func
        "LED Blink task",    // Task name
        2048,                // Stack size
        NULL,                // Task params
        1,                   // Task priority
        &ledBlinkTaskHandle  // Task handle            
    );

    xTaskCreate(
        CounterTask,        // Task func
        "Counter task",    // Task name
        2048,                // Stack size
        NULL,                // Task params
        1,                   // Task priority
        &CounterTaskHandle  // Task handle            
    );

    

}

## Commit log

2025-05-24 Added custom VFD library
2025-05-24 Added backups to ignore list
2025-05-24 General schematic layout
2025-05-25 Added power supply part of schematic
2025-05-25 Added linear regulator for filament voltage
2025-05-25 Generated ibom
2025-05-25 Added sensors and general feature ideas
2025-05-25 Added TVS diodes
2025-05-26 Added TVS and packages for components
2025-05-28 Added custom footprints for VEML light sensor, added sensors and RTC, pull-ups for I2C
2025-05-30 Added footprints
2025-05-30 Added custom USB-C footprint
2025-05-30 Initial component placement
2025-05-31 Footprint placement progress
2025-05-31 VEML3235SL model
2025-05-31 Created separator_pcb
2025-05-31 Finished separator board
2025-05-31 Footprint placement done, PWR needs connecting
2025-06-01 Layout done, generated fabrication files
2025-06-01 Readded light sensor 3D model
2025-06-01 Rendered images of main board
2025-06-02 Modified circuit to use synchronous grid clock on all modules
2025-06-02 First commit for side module board
2025-06-03 Fixed placement of mounting holes and pin headers
2025-06-03 Layout done
2025-06-03 Updated gitignore
2025-06-03 Updated gitignore to not track <pcb name>/production/backups
2025-06-04 Moved cell battery, generated STEP files
2025-06-04 Added 3D model for the case
2025-06-11 Added models for VFD and socket
2025-06-13 Case design rev. 1 finished
2025-06-13 MInor change in case feet
2025-06-14 Blender import for rendering
2025-06-14 Added images to readme.md
2025-06-16 Minor chamfer in Case. Generated .step files for print
2025-06-17 Replaced capacitor footprints with EIA-3216
2025-06-17 Replaced capacitor footprint with EIA-3216
2025-06-17 Generated production files
2025-06-19 Generated BOM
2025-06-22 Generated pcb3d files and rendered images
2025-06-22 Updated gitignore to ignore .blend1 files
2025-06-22 Updated repo readme
2025-06-22 Updated file names
2025-06-22 Cropped image to better fit
2025-06-22 Added image for social preview
2025-07-13 First commit for sw
2025-07-13 Added folders to gitignore
2025-07-25 Working counter and display driver for middle VFDs
2025-07-27 Added RTC with NTP project
2025-07-27 Created schematic and pinout files for ESP32-S3
2025-07-28 Removed unused handle
2025-08-15 First commit for this code
2025-08-15 Missing files from last commit
2025-08-17 Working implementation
2025-08-17 Added experimental functions for displaying strings
2025-08-18 Rewriting vfd_value_str to take strings as input
2025-08-18 Repo sync
2025-08-18 Removed files from index
2025-08-18 Working string input
2025-08-18 Adjusted hole diameter
2025-08-18 Updated the VFD library from vfd_blink
2025-08-23 Set ONLINE_MODE to 1
2025-08-23 Removed config files
2025-08-23 Modified hole diameters for heated insert holes, changed hole to accept a nut
2025-08-23 Added holes for screw heads
2025-08-24 Modified supports and hole height
2025-09-25 Modified parts to fit better
